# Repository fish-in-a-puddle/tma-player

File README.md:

# The Magnus Archives-themed Podcast Player

*a project by fish-in-a-puddle*

.png>) 
   .png>) 

.png>)

.png>) 

.png>)

An ESP32-based MP3 player designed to look like a handheld tape recorder like the one used in the podcast "The Magnus Archives" containing every episode of the podcast. It uses a DFPlayer Mini module to play the audio and 11 SK6812E LEDs to add green lighting under the control buttons and "speaker" grill. A 0.91" OLED display allows you to select which episode you would like to listen to and shows what's playing.

**No AI was used in making of this project**

## Why I made this project

I started listening to The Magnus Archives, a horror podcast that tells the story through a series of tape recordings, a few months ago. Throughout the series, the tape recorders almost became characters of their own and I couldn't shake the idea of listening to the story on a replica of one. The hardest part of the project was definitely 3D-modeling the case itself, but I learned a lot about using Fusion, as well as designing PCBs.

## How to assemble 

Assembling the hardware itself should not be difficult. Once you have all the parts (as listed in Bill of Materials below) you will simply have to solder them onto their respective PCBs. To connect the two PCBs, you will need to take nine female-to-female jumper wires and connect each pin on the main PCB to its mate (5v to 5v, GND to GND, DIN to DIN, etc.). To connect the OLED screen to the main PCB, take four more female-to-female jumper wires and connect the pins of the display to the pin headers on the PCB as shown:

.png>)

You will also need to wire the battery, charging board, step-up module and on/off switch as shown. These parts will be arranged in the case later, so it's important not to make the wires too short or too long.

.png>)

Before putting the whole thing together, you will need to flash the firmware to the ESP32, as it will not be accessible when the main PCB is in the case. To flash the code, you will need to have the Arduino IDE installed (download the latest version [here](https://www.arduino.cc/en/software/)). You will also need to have the "esp32" board pack and a few useful libraries installed, which is very easy to do. Just go to "Boards" and search "esp32" and click install on the pack. Make sure that you select the pack with the title in all lowercase. To download the libraries, go the "Libraries" and install these libraries:

- Adafruit_GFX
- Adafruit_SSD1306
- FastLed
- DFPlayerMini_Fast

 Once your IDE is all set up, go to the file "[player-code.ino](https://github.com/fish-in-a-puddle/tma-player/blob/main/player-code.ino)" and copy its contents. Paste them into the IDE. Connect the ESP32 to your computer via USB. Select your board and port in the dropdown menu at the top of your screen and click "Upload". Boom! Code uploaded!

 The code is not the only thing you'll need to download, though. The DFPlayer Mini is a tiny MP3 player that reads audio files from a microSD card. The files have to be named and organized a certain way, though, in order for the DFPlayer to be able to play them. But we're getting a bit ahead of ourselves. Before organizing the files, you need to download them. Unfortunately, I can't provide them all here as the podcast is not mine to distribute, but I can show you how to get them yourself. You can download them all from YouTube with a third-party downloader like [this one](https://apps.microsoft.com/detail/xpffdcd2ps6dgh?hl=en-US&gl=CA) that I used. All 200 episodes can be found on [this playlist](https://www.youtube.com/playlist?list=PLSbuB1AyaJk8zTF3nE2KRxuixG_A5gBKJ) and you can download the entire playlist at once (plus the Oh... Hello. extra [here](https://youtu.be/0ue0QZ2ED9w?si=zBTRZmKF8gP67J3-)). Be forewarned, it may take several hours and altogether is about 4.5GB. When the files are downloaded, copy them over to your microSD card (which must be formatted as FAT32!) and rename them as 0001, 0002, 0003, etc. If you need more info, check out [this article](https://printed-droid.com/kb/dfplayer-mini-guide/) by Printed Droid - it helped me a lot. If you want, you can also cut out some of the ads in an audio editing software like Audacity.

Back to the hardware! 3D print the top and bottom of the case and and place the main PCB inside the bottom part. The microSD card slot and headphone jack should line up with the holes on the top of the case. Next, take the side PCB and fit it into the large slot on the right side of the bottom part. Secure it in place with electrical tape so it doesn't slide. Right next to the headphone jack, there is a large slot for the charging board. Position the board so the charging port is accessible and secure it with electrical tape. Do the same for the on/off switch slot above it. Place the OLED display on the top part so it is visible through the rectangular hole and - you guessed  it - secure it with electrical tape. As you put the top and bottom parts together, you may have to get a little creative arranging the battery and wires in the case. Once everything is packed away, screw together the top and bottom with four M3 screws.

## Bill of Materials

|Part                       |Quantity|My Source                                                                                                                                                                                                                                                                                                                                                                                                                                                                                                                                                                                                                                                                                                                                                                     |Price (USD)|Shipping      |Alternate Source (if necessary)                                                                                                                                                                                                                                                                                                                                                                                                                                                                                                                                                                                                                                                                                                                                                        |Price (USD)|Shipping      |Notes                                             |
|---------------------------|--------|------------------------------------------------------------------------------------------------------------------------------------------------------------------------------------------------------------------------------------------------------------------------------------------------------------------------------------------------------------------------------------------------------------------------------------------------------------------------------------------------------------------------------------------------------------------------------------------------------------------------------------------------------------------------------------------------------------------------------------------------------------------------------|-----------|--------------|---------------------------------------------------------------------------------------------------------------------------------------------------------------------------------------------------------------------------------------------------------------------------------------------------------------------------------------------------------------------------------------------------------------------------------------------------------------------------------------------------------------------------------------------------------------------------------------------------------------------------------------------------------------------------------------------------------------------------------------------------------------------------------------|-----------|--------------|--------------------------------------------------|
|Seeeduino Xiao ESP-32-C3   | 1      | https://www.aliexpress.com/item/1005008791937363.html?spm=a2g0o.productlist.main.1.4de91acfmMRQxW&algo_pvid=2fee8b63-2bf0-4724-bf66-3179fd38bab1&algo_exp_id=2fee8b63-2bf0-4724-bf66-3179fd38bab1-0&pdp_ext_f=%7B%22order%22%3A%221596%22%2C%22eval%22%3A%221%22%2C%22fromPage%22%3A%22search%22%7D&pdp_npi=6%40dis%21CAD%2113.05%2110.17%21%21%219.07%217.07%21%402101e75417932184264203459e0fe8%2112000052930246748%21sea%21CA%210%21ABX%211%210%21n_tag%3A-29910%3Bd%3Aae79d1aa%3Bm03_new_user%3A-29895%3BpisId%3A5000000218656158&curPageLogUid=wpoppYNjFX4K&utparam-url=scene%3Asearch%7Cquery_from%3A%7Cx_object_id%3A1005008791937363%7C_p_origin_prod%3A                                                                                                             | $9.27     | Free shipping| x                                                                                                                                                                                                                                                                                                                                                                                                                                                                                                                                                                                                                                                                                                                                                                                     | x         | x            | None                                             |
|DFPlayer Mini (YX5200-24QS)| 1      | https://www.aliexpress.com/item/1005003432670517.html?spm=a2g0o.productlist.main.6.b79435a6qtJZhj&algo_pvid=8a43199a-29af-4fc8-b324-c76739e5a8f2&algo_exp_id=8a43199a-29af-4fc8-b324-c76739e5a8f2-5&pdp_ext_f=%7B%22order%22%3A%221037%22%2C%22eval%22%3A%221%22%2C%22fromPage%22%3A%22search%22%7D&pdp_npi=6%40dis%21CAD%215.17%214.19%21%21%2123.96%2119.42%21%402101c28d17932189515971049e0efb%2112000025764114712%21sea%21CA%210%21ABX%211%210%21n_tag%3A-29910%3Bd%3Aae79d1aa%3Bm03_new_user%3A-29895&curPageLogUid=lcZ3ZxaTiNQR&utparam-url=scene%3Asearch%7Cquery_from%3A%7Cx_object_id%3A1005003432670517%7C_p_origin_prod%3A                                                                                                                                        | $3.65     | $5.42        | x                                                                                                                                                                                                                                                                                                                                                                                                                                                                                                                                                                                                                                                                                                                                                                                     | x         | x            | None                                             |
|Headphone jack             | 1      | https://www.aliexpress.com/item/4000114275750.html?spm=a2g0o.productlist.main.14.45ce323943IJGD&algo_pvid=0fef7f45-504e-4663-8247-9c40bcd4e426&algo_exp_id=0fef7f45-504e-4663-8247-9c40bcd4e426-13&pdp_ext_f=%7B%22order%22%3A%2236%22%2C%22eval%22%3A%221%22%2C%22fromPage%22%3A%22search%22%7D&pdp_npi=6%40dis%21CAD%212.93%211.71%21%21%2113.58%217.93%21%402101ca8b17932239827126302e0f03%2112000032841975173%21sea%21CA%210%21ABX%211%210%21n_tag%3A-29910%3Bd%3Aae79d1aa%3Bm03_new_user%3A-29895%3BpisId%3A5000000218656158&curPageLogUid=AsbevJNFO0kb&utparam-url=scene%3Asearch%7Cquery_from%3A%7Cx_object_id%3A4000114275750%7C_p_origin_prod%3A                                                                                                                    | $2.18     | Free shipping| x                                                                                                                                                                                                                                                                                                                                                                                                                                                                                                                                                                                                                                                                                                                                                                                     | x         | x            | This source comes in a pack of 10                |
|0.91 OLED                  | 1      | https://www.aliexpress.com/item/1005008918700196.html?spm=a2g0o.productlist.main.2.7de8411fMeiJOd&algo_pvid=0fc6a299-644e-44f4-b982-0728ee1bc7f9&algo_exp_id=0fc6a299-644e-44f4-b982-0728ee1bc7f9-1&pdp_ext_f=%7B%22order%22%3A%22908%22%2C%22spu_best_type%22%3A%22price%22%2C%22eval%22%3A%221%22%2C%22fromPage%22%3A%22search%22%7D&pdp_npi=6%40dis%21CAD%213.60%211.74%21%21%212.47%211.19%21%40210327b017946691312165659e0e37%2112000047202792616%21sea%21CA%210%21ABX%211%210%21n_tag%3A-29910%3Bd%3Aefcbf61%3Bm03_new_user%3A-29895%3BpisId%3A5000000218625931&curPageLogUid=dVpT9IM6Sb9L&utparam-url=scene%3Asearch%7Cquery_from%3A%7Cx_object_id%3A1005008918700196%7C_p_origin_prod%3A                                                                             | $2.58     | Free shipping| x                                                                                                                                                                                                                                                                                                                                                                                                                                                                                                                                                                                                                                                                                                                                                                                     | x         | x            | Buy the version with white text                  |
|Toggle switch              | 1      | https://www.aliexpress.com/item/1005008304338583.html?spm=a2g0o.productlist.main.4.7a6915bapGlbZB&aem_p4p_detail=202611211749531201418159040720001920699&algo_pvid=33cdea45-54ac-4164-86e0-36b4e3f8295f&algo_exp_id=33cdea45-54ac-4164-86e0-36b4e3f8295f-3&pdp_ext_f=%7B%22order%22%3A%223730%22%2C%22eval%22%3A%221%22%2C%22fromPage%22%3A%22search%22%7D&pdp_npi=6%40dis%21CAD%216.66%211.75%21%21%2130.28%217.92%21%402101c4ea17953121930127537e0ff8%2112000044555585173%21sea%21CA%210%21ABX%211%210%21n_tag%3A-29910%3Bd%3Aefcbf61%3Bm03_new_user%3A-29895%3BpisId%3A5000000218625935&curPageLogUid=Mz6zwQEAy92a&utparam-url=scene%3Asearch%7Cquery_from%3A%7Cx_object_id%3A1005008304338583%7C_p_origin_prod%3A&search_p4p_id=202611211749531201418159040720001920699_1| $4.64     | Free shipping| x                                                                                                                                                                                                                                                                                                                                                                                                                                                                                                                                                                                                                                                                                                                                                                                     | x         | x            |Comes in pack of 10                               |
|Charging board             | 1      | https://www.aliexpress.com/item/1005007176376691.html?spm=a2g0o.productlist.main.5.78ae2a94npf7VK&algo_pvid=84e47fdb-b963-4705-8d50-a8167387f458&algo_exp_id=84e47fdb-b963-4705-8d50-a8167387f458-4&pdp_ext_f=%7B%22order%22%3A%224529%22%2C%22eval%22%3A%221%22%2C%22fromPage%22%3A%22search%22%7D&pdp_npi=6%40dis%21CAD%213.56%211.73%21%21%2116.39%217.96%21%4021030f8317921823444828610e0f04%2112000044697950819%21sea%21CA%210%21ABX%211%210%21n_tag%3A-29910%3Bd%3A59ac8ea0%3Bm03_new_user%3A-29895%3BpisId%3A5000000218640858&curPageLogUid=oX28Jdw7Dcfm&utparam-url=scene%3Asearch%7Cquery_from%3A%7Cx_object_id%3A1005007176376691%7C_p_origin_prod%3A                                                                                                              | $2.50     | Free shipping| x                                                                                                                                                                                                                                                                                                                                                                                                                                                                                                                                                                                                                                                                                                                                                                                     | x         | x            | Buy Type-c version                               |
|3.7 to 5v converter        | 1      | https://www.aliexpress.com/item/1005009886614988.html?spm=a2g0o.productlist.main.15.7bd941bahfQ4ew&algo_pvid=f71aa114-ff81-4c28-bada-3685d00938ec&algo_exp_id=f71aa114-ff81-4c28-bada-3685d00938ec-12&pdp_ext_f=%7B%22order%22%3A%22319%22%2C%22eval%22%3A%221%22%2C%22fromPage%22%3A%22search%22%7D&pdp_npi=6%40dis%21CAD%211.83%211.19%21%21%211.26%210.82%21%402101d3fe17921826331035682e0fbb%2112000050482123027%21sea%21CA%210%21ABX%211%210%21n_tag%3A-29910%3Bd%3A59ac8ea0%3Bm03_new_user%3A-29895&curPageLogUid=CW98wpodDnyn&utparam-url=scene%3Asearch%7Cquery_from%3A%7Cx_object_id%3A1005009886614988%7C_p_origin_prod%3A                                                                                                                                         | $1.28     | $6.00        | x                                                                                                                                                                                                                                                                                                                                                                                                                                                                                                                                                                                                                                                                                                                                                                                     | x         | x            | None                                             |
|Lipo battery               | 1      | https://www.aliexpress.com/item/1005009939339870.html?spm=a2g0o.productlist.main.18.73b46ee1murCfL&algo_pvid=50d0af34-6228-4874-9fac-6284729655b3&algo_exp_id=50d0af34-6228-4874-9fac-6284729655b3-17&pdp_ext_f=%7B%22order%22%3A%22206%22%2C%22spu_best_type%22%3A%22price%22%2C%22eval%22%3A%221%22%2C%22fromPage%22%3A%22search%22%7D&pdp_npi=6%40dis%21CAD%2110.75%216.45%21%21%2149.81%2129.89%21%4021030cd817932242519431859e0d3f%2112000050631004477%21sea%21CA%210%21ABX%211%210%21n_tag%3A-29910%3Bd%3Aae79d1aa%3Bm03_new_user%3A-29895&curPageLogUid=QlHpURKrjpsB&utparam-url=scene%3Asearch%7Cquery_from%3A%7Cx_object_id%3A1005009939339870%7C_p_origin_prod%3A                                                                                                  | $7.53     | $2.96        | x                                                                                                                                                                                                                                                                                                                                                                                                                                                                                                                                                                                                                                                                                                                                                                                     | x         | x            | None                                             |
|SK6812MINI-E LED           | 11     | Leftovers from Hack Club's Hackpad Kit (https://hackpad.hackclub.com/)                                                                                                                                                                                                                                                                                                                                                                                                                                                                                                                                                                                                                                                                                                       | $0        | $0           | https://www.aliexpress.com/item/1005007863635868.html?spm=a2g0o.productlist.main.1.71e51c3cifbRkD&algo_pvid=96cd1d50-48f6-47d0-9c8d-db0703947e2a&algo_exp_id=96cd1d50-48f6-47d0-9c8d-db0703947e2a-0&pdp_ext_f=%7B%22order%22%3A%22635%22%2C%22eval%22%3A%221%22%2C%22fromPage%22%3A%22search%22%7D&pdp_npi=6%40dis%21CAD%216.87%211.75%21%21%214.68%211.19%21%402101de2517953112525471063e0eec%2112000042594617264%21sea%21CA%210%21ABX%211%210%21n_tag%3A-29910%3Bd%3Aefcbf61%3Bm03_new_user%3A-29895%3BpisId%3A5000000218625935&curPageLogUid=0hEvfxi8ywtW&utparam-url=scene%3Asearch%7Cquery_from%3A%7Cx_object_id%3A1005007863635868%7C_p_origin_prod%3A                                                                                                                          | $4.78     | Free shipping| Alternate source comes in pack of 100            |
|1N4148 Diode               | 1      | Leftovers from Hack Club's Hackpad Kit (https://hackpad.hackclub.com)                                                                                                                                                                                                                                                                                                                                                                                                                                                                                                                                                                                                                                                                                                        | $0        | $0           | https://www.aliexpress.com/item/1005012285965228.html?spm=a2g0o.productlist.main.28.79e7482d6HQ6Nf&aem_p4p_detail=202611211738254444529954834100000471533&algo_pvid=434f4d44-b9f7-4691-8bfc-d5242381183e&algo_exp_id=434f4d44-b9f7-4691-8bfc-d5242381183e-27&pdp_ext_f=%7B%22order%22%3A%2211%22%2C%22spu_best_type%22%3A%22price%22%2C%22eval%22%3A%221%22%2C%22fromPage%22%3A%22search%22%7D&pdp_npi=6%40dis%21CAD%212.22%211.82%21%21%2110.09%218.27%21%402101c4b817953115053577203e0e78%2112000057989572495%21sea%21CA%210%21ABX%211%210%21n_tag%3A-29910%3Bd%3Aefcbf61%3Bm03_new_user%3A-29895&curPageLogUid=KVPwmbDF8rbQ&utparam-url=scene%3Asearch%7Cquery_from%3A%7Cx_object_id%3A1005012285965228%7C_p_origin_prod%3A&search_p4p_id=202611211738254444529954834100000471533_7| $6.39     | Free shipping| Alternate source comes in pack of 100            |
|Cherry MX keyswitches      | 5      | Leftovers from Hack Club's Hackpad Kit (https://hackpad.hackclub.com)                                                                                                                                                                                                                                                                                                                                                                                                                                                                                                                                                                                                                                                                                                        | $0        | $0           | https://www.aliexpress.com/item/1005012832907656.html?spm=a2g0o.productlist.main.6.516b44cc2K1o9K&algo_pvid=d45f9856-152a-4c3e-987f-c93a21a25b67&algo_exp_id=d45f9856-152a-4c3e-987f-c93a21a25b67-5&pdp_ext_f=%7B%22order%22%3A%2260%22%2C%22eval%22%3A%221%22%2C%22fromPage%22%3A%22search%22%7D&pdp_npi=6%40dis%21CAD%218.13%211.75%21%21%215.54%211.19%21%402101e56817953146701488274e0e89%2112000059458181010%21sea%21CA%210%21ABX%211%210%21n_tag%3A-29910%3Bd%3Aefcbf61%3Bm03_new_user%3A-29895%3BpisId%3A5000000218625935&curPageLogUid=AAqFQ5bkuN9i&utparam-url=scene%3Asearch%7Cquery_from%3A%7Cx_object_id%3A1005012832907656%7C_p_origin_prod%3A                                                                                                                           | $5.66     | Free shipping| Alternate source comes in pack of 10             |
|Keycaps                    | 5      | Leftovers from Hack Club's Hackpad Kit (https://hackpad.hackclub.com)                                                                                                                                                                                                                                                                                                                                                                                                                                                                                                                                                                                                                                                                                                        | $0        | $0           | https://www.aliexpress.com/item/1005010545409350.html?spm=a2g0o.productlist.main.21.7734599cbfPriz&algo_pvid=cc549d13-fe82-422f-8342-e8792835ce0d&algo_exp_id=cc549d13-fe82-422f-8342-e8792835ce0d-20&pdp_ext_f=%7B%22order%22%3A%22388%22%2C%22eval%22%3A%221%22%2C%22fromPage%22%3A%22search%22%7D&pdp_npi=6%40dis%21CAD%215.33%211.75%21%21%213.63%211.19%21%402101c4b817953149577943262e0efc%2112000052767672810%21sea%21CA%210%21ABX%211%210%21n_tag%3A-29910%3Bd%3Aefcbf61%3Bm03_new_user%3A-29895%3BpisId%3A5000000218625935&curPageLogUid=jElAVqFtryO5&utparam-url=scene%3Asearch%7Cquery_from%3A%7Cx_object_id%3A1005010545409350%7C_p_origin_prod%3A                                                                                                                        | $3.71     | Free shipping| Alternate source comes in pack of 10             |
|25mm M3 screws             | 4      | https://www.aliexpress.com/item/1005005070119421.html?spm=a2g0o.productlist.main.1.2b886e1fgwFFsl&algo_pvid=aae8f3ad-208c-46b6-ab58-f4c01dd6ced7&algo_exp_id=aae8f3ad-208c-46b6-ab58-f4c01dd6ced7-0&pdp_ext_f=%7B%22order%22%3A%2239084%22%2C%22spu_best_type%22%3A%22price%22%2C%22eval%22%3A%221%22%2C%22fromPage%22%3A%22search%22%7D&pdp_npi=6%40dis%21CAD%212.51%211.75%21%21%211.71%211.19%21%4021030f8317955492549322586e0eb6%2112000031519353305%21sea%21CA%210%21ABX%211%210%21n_tag%3A-29910%3Bd%3Aefcbf61%3Bm03_new_user%3A-29895%3BpisId%3A5000000218625934&curPageLogUid=QeZJmcAGx4kg&utparam-url=scene%3Asearch%7Cquery_from%3A%7Cx_object_id%3A1005005070119421%7C_p_origin_prod%3A                                                                           | $3.86     | Free shipping| x                                                                                                                                                                                                                                                                                                                                                                                                                                                                                                                                                                                                                                                                                                                                                                                     | x         | x            | Comes in pack of 50                              |
|1kohm resistor             | 4      | https://www.aliexpress.com/item/1005002580178929.html?spm=a2g0o.productlist.main.22.166b6d60KBE4U0&aem_p4p_detail=202611211806376467483684059500001906962&algo_pvid=edbc9152-e65f-4729-bbd9-f900f122d453&algo_exp_id=edbc9152-e65f-4729-bbd9-f900f122d453-19&pdp_ext_f=%7B%22order%22%3A%22679%22%2C%22eval%22%3A%221%22%2C%22fromPage%22%3A%22search%22%7D&pdp_npi=6%40dis%21CAD%214.59%211.75%21%21%213.13%211.20%21%402101ea8f17953131974298811e08a8%2112000021245046656%21sea%21CA%210%21ABX%211%210%21n_tag%3A-29910%3Bd%3Aefcbf61%3Bm03_new_user%3A-29895%3BpisId%3A5000000218625935&curPageLogUid=Fq1QoduLe98H&utparam-url=scene%3Asearch%7Cquery_from%3A%7Cx_object_id%3A1005002580178929%7C_p_origin_prod%3A&search_p4p_id=202611211806376467483684059500001906962_5| $4.14     | Free shipping| x                                                                                                                                                                                                                                                                                                                                                                                                                                                                                                                                                                                                                                                                                                                                                                                     | x         | x            | This source comes in pack of 20                  |
|32gb MicroSD card          | 1      | https://www.aliexpress.com/item/1005007498167692.html?spm=a2g0o.productlist.main.17.fcba288bFLAcSD&algo_pvid=f6bce296-19da-42ea-9d59-f8da1a0c549c&algo_exp_id=f6bce296-19da-42ea-9d59-f8da1a0c549c-16&pdp_ext_f=%7B%22order%22%3A%2235229%22%2C%22spu_best_type%22%3A%22price%22%2C%22eval%22%3A%221%22%2C%22fromPage%22%3A%22search%22%7D&pdp_npi=6%40dis%21CAD%2112.13%211.75%21%21%218.27%211.20%21%402101ca9517953119118377072e0d41%2112000041032084439%21sea%21CA%210%21ABX%211%210%21n_tag%3A-29910%3Bd%3Aefcbf61%3Bm03_new_user%3A-29895%3BpisId%3A5000000218625936&curPageLogUid=mZfRL4Fc1bcW&utparam-url=scene%3Asearch%7Cquery_from%3A%7Cx_object_id%3A1005007498167692%7C_p_origin_prod%3A                                                                        | $8.45     | Free shipping| x                                                                                                                                                                                                                                                                                                                                                                                                                                                                                                                                                                                                                                                                                                                                                                                     | x         | x            | None                                             |
|Front PCB                  | 1      | JLCPCB                                                                                                                                                                                                                                                                                                                                                                                                                                                                                                                                                                                                                                                                                                                                                                       | $10.30    | $8.92        | x                                                                                                                                                                                                                                                                                                                                                                                                                                                                                                                                                                                                                                                                                                                                                                                     | x         | x            | Order on the JLC Desktop version for better price|
|Side PCB                   | 1      | JLCPCB                                                                                                                                                                                                                                                                                                                                                                                                                                                                                                                                                                                                                                                                                                                                                                       | $2.10     | $1.50        | x                                                                                                                                                                                                                                                                                                                                                                                                                                                                                                                                                                                                                                                                                                                                                                                     | x         | x            | Order in the JLC Desktop version for better price|
|Parts total:               | $58.62 |                                                                                                                                                                                                                                                                                                                                                                                                                                                                                                                                                                                                                                                                                                                                                                              |           |              |                                                                                                                                                                                                                                                                                                                                                                                                                                                                                                                                                                                                                                                                                                                                                                                       |           |              |                                                  |
|Shipping total:            | $24.80 |                                                                                                                                                                                                                                                                                                                                                                                                                                                                                                                                                                                                                                                                                                                                                                              |           |              |                                                                                                                                                                                                                                                                                                                                                                                                                                                                                                                                                                                                                                                                                                                                                                                       |           |              |                                                  |
|Final total:               | $83.42 |                                                                                                                                                                                                                                                                                                                                                                                                                                                                                                                                                                                                                                                                                                                                                                              |           |              |                                                                                                                                                                                                                                                                                                                                                                                                                                                                                                                                                                                                                                                                                                                                                                                       |           |              |                                                  |

## Credits

References, libraries and Kicad footprints I used to make this project

- Seeeduino Xiao ESP-32-C3 Kicad footprint - https://gitlab.fabcloud.org/ricardo.marques/kicad/-/blob/master/fab.pretty/SeeedStudio_XIAO_ESP32C3.kicad_mod
- Seeeduino Xiao ESP-32-C3 Kicad symbol - https://github.com/VectorSpaceHQ/XIAO_ESP32C3/blob/main/xiao_esp32c3.kicad_sym 
- DFPlayer Mini Kicad footprint - https://github.com/MrChunckuee-Electronics/KiCad_Libraries/blob/master/footprints/MCE_Modules.pretty/DFPlayer_MiniMP3.kicad_mod
- DFPlayer Mini Kicad schematic symbol - https://github.com/MrChunckuee-Electronics/KiCad_Libraries/blob/master/symbols/MCE_Modules.kicad_sym
- DFPlayer Mini wiring - https://reprage.com/posts/2018-05-08-dfplayer-mini-cheat-sheet/, https://www.reddit.com/r/arduino/comments/1n1itlh/getting_nothing_out_of_dfplayer/, https://www.printed-droid.com/kb/dfplayer-mini-guide/
- FastLED library examples: https://github.com/FastLED/FastLED/blob/master/cookbook/basic-patterns/animations.md
- DFPlayerMini_Fast library example: https://github.com/PowerBroker2/DFPlayerMini_Fast/blob/master/examples/example/example.ino
- Adafruit SSD1306 OLED library: https://github.com/adafruit/Adafruit_SSD1306
- YouTube downloader/mp3 converter for Windows: https://apps.microsoft.com/detail/xpffdcd2ps6dgh?hl=en-US&gl=CA
- The Magnus Archives full series on YouTube: https://www.youtube.com/playlist?list=PLSbuB1AyaJk8zTF3nE2KRxuixG_A5gBKJ
- Cherry MX keycap used for model: https://www.printables.com/model/118708-simple-cherry-mx-keycap/files
- Kicad care package from Hackpad program (used SK6812MINI-E footprint): https://github.com/hackclub/hackpad/releases/tag/v0.1-bugfix

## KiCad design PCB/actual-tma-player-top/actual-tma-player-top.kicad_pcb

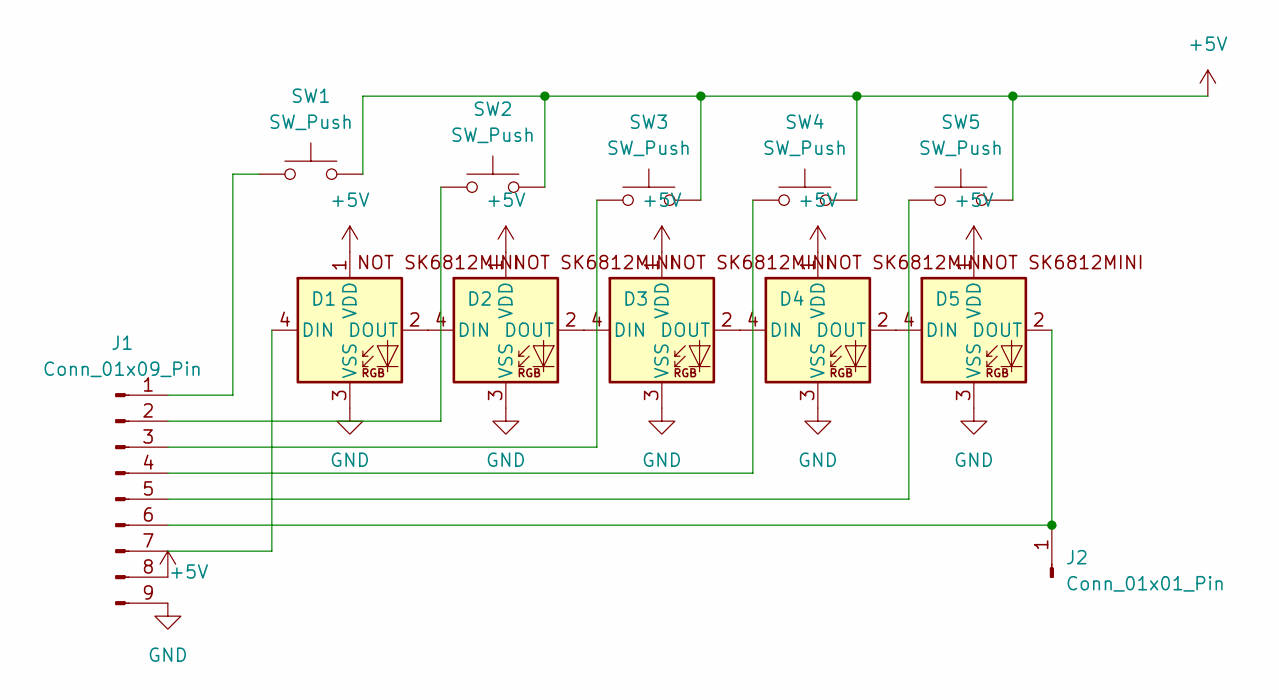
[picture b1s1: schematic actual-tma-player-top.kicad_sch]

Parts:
D1, D2, D3, D4, D5: SK6812MINI-E; SK6812MINI-E_fixed
J1: Conn_01x09_Pin; PinHeader_1x09_P1.00mm_Vertical
J2: Conn_01x01_Pin; PinHeader_1x01_P1.00mm_Vertical
SW1, SW2, SW3, SW4, SW5: SW_Push; SW_Cherry_MX_1.00u_PCB

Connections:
+5V: D1.1 (VDD), D2.1 (VDD), D3.1 (VDD), D4.1 (VDD), D5.1 (VDD), J1.8, SW1.2, SW2.2, SW3.2, SW4.2, SW5.2
GND: D1.3 (VSS), D2.3 (VSS), D3.3 (VSS), D4.3 (VSS), D5.3 (VSS), J1.9
unnamed: D1.4 (DIN), J1.7
unnamed: D1.2 (DOUT), D2.4 (DIN)
unnamed: D2.2 (DOUT), D3.4 (DIN)
unnamed: D3.2 (DOUT), D4.4 (DIN)
unnamed: D4.2 (DOUT), D5.4 (DIN)
unnamed: D5.2 (DOUT), J1.6, J2.1 (Pin_1_1)
unnamed: J1.1, SW1.1
unnamed: J1.2, SW2.1
unnamed: J1.3, SW3.1
unnamed: J1.4, SW4.1
unnamed: J1.5, SW5.1

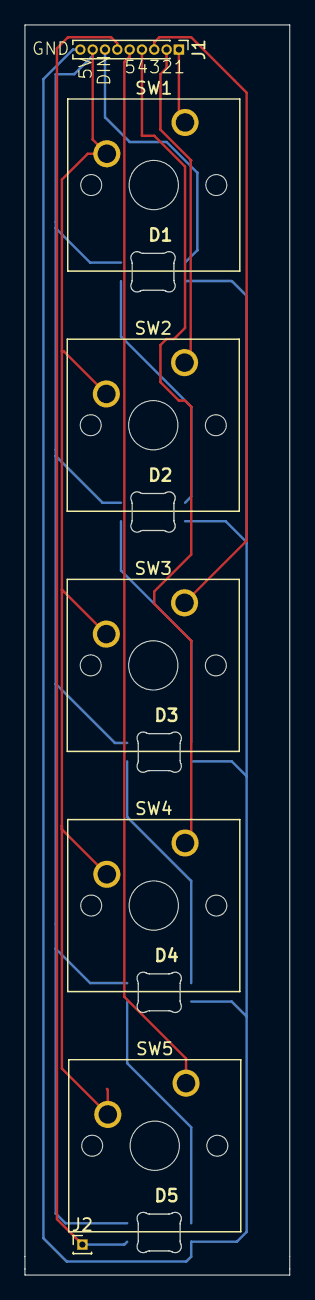
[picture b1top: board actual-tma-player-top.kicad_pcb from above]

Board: 2 copper layers, 21.5 x 101.5 mm, 12 parts (0 on the bottom side), 13 nets.

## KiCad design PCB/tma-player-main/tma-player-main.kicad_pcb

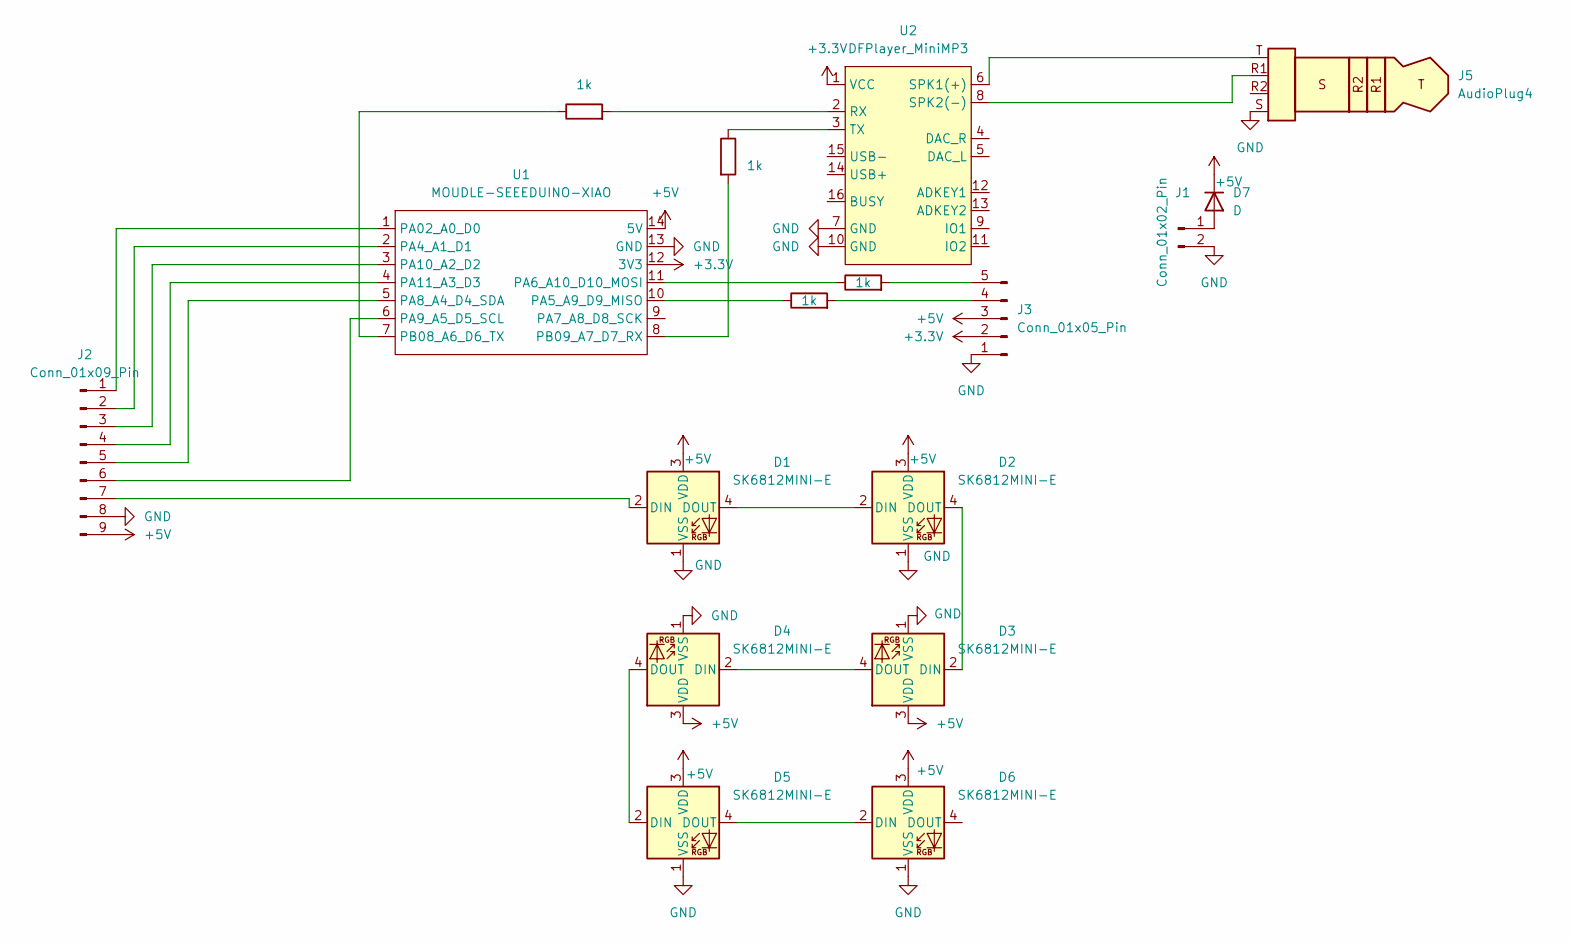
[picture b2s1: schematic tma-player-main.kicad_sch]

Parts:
D1, D2, D3, D4, D5, D6: SK6812MINI-E; LED_SK6812MINI-E_3.2x2.8mm_P1.5mm_ReverseMount
D7: D; D_DO-35_SOD27_P7.62mm_Horizontal
J1: Conn_01x02_Pin; PinHeader_1x02_P1.00mm_Horizontal
J2: Conn_01x09_Pin; PinHeader_1x09_P1.00mm_Vertical
J3: Conn_01x05_Pin; PinHeader_1x05_P1.00mm_Vertical
J5: AudioPlug4; Jack_3.5mm_PJ320D_Horizontal
R1, R2: 1k; R_Axial_DIN0309_L9.0mm_D3.2mm_P15.24mm_Horizontal
R3, R4: 1k; R_Axial_DIN0207_L6.3mm_D2.5mm_P15.24mm_Horizontal
U1: MOUDLE-SEEEDUINO-XIAO; SeeedStudio_XIAO_ESP32C3
U2: DFPlayer_MiniMP3

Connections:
+3.3V: J3.2, U1.12 (3V3), U2.1 (VCC)
+5V: D1.3 (VDD), D2.3 (VDD), D3.3 (VDD), D4.3 (VDD), D5.3 (VDD), D6.3 (VDD), D7.1 (K), J2.9, J3.3, U1.14 (5V); also elsewhere on the board
GND: D1.1 (VSS), D2.1 (VSS), D3.1 (VSS), D4.1 (VSS), D5.1 (VSS), D6.1 (VSS), J1.2, J2.8, J3.1, J5.S, U1.13 (GND), U2.7 (GND), U2.10 (GND)
unnamed: D1.2 (DIN), J2.7
unnamed: D1.4 (DOUT), D2.2 (DIN)
unnamed: D2.4 (DOUT), D3.2 (DIN)
unnamed: D3.4 (DOUT), D4.2 (DIN)
unnamed: D4.4 (DOUT), D5.2 (DIN)
unnamed: D5.4 (DOUT), D6.2 (DIN)
unnamed 9: D7.2 (A), J1.1; also elsewhere on the board
unnamed: J2.1, U1.1 (PA02_A0_D0)
unnamed: J2.2, U1.2 (PA4_A1_D1)
unnamed: J2.3, U1.3 (PA10_A2_D2)
unnamed: J2.4, U1.4 (PA11_A3_D3)
unnamed: J2.5, U1.5 (PA8_A4_D4_SDA)
unnamed: J2.6, U1.6 (PA9_A5_D5_SCL)
unnamed: J3.4, R4.2
unnamed: J3.5, R3.2
unnamed: R4.1, U1.10 (PA5_A9_D9_MISO)
unnamed: R3.1, U1.11 (PA6_A10_D10_MOSI)
unnamed: R1.1, U1.7 (PB08_A6_D6_TX)
unnamed: R2.2, U1.8 (PB09_A7_D7_RX)
unnamed: R1.2, U2.2 (RX)
unnamed: J5.T, U2.6 (SPK1(+))
unnamed: J5.R1, U2.8 (SPK2(-))
unnamed: R2.1, U2.3 (TX)

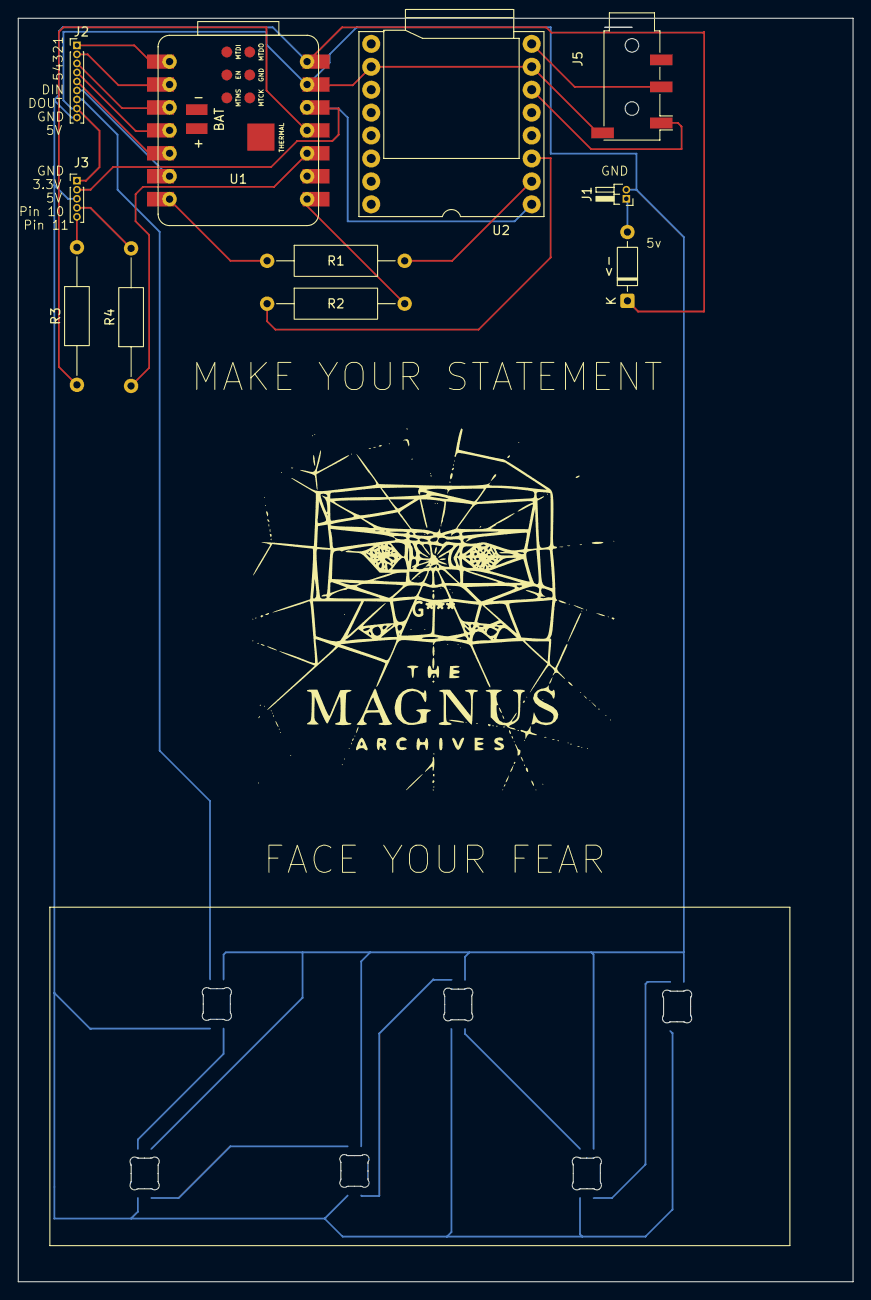
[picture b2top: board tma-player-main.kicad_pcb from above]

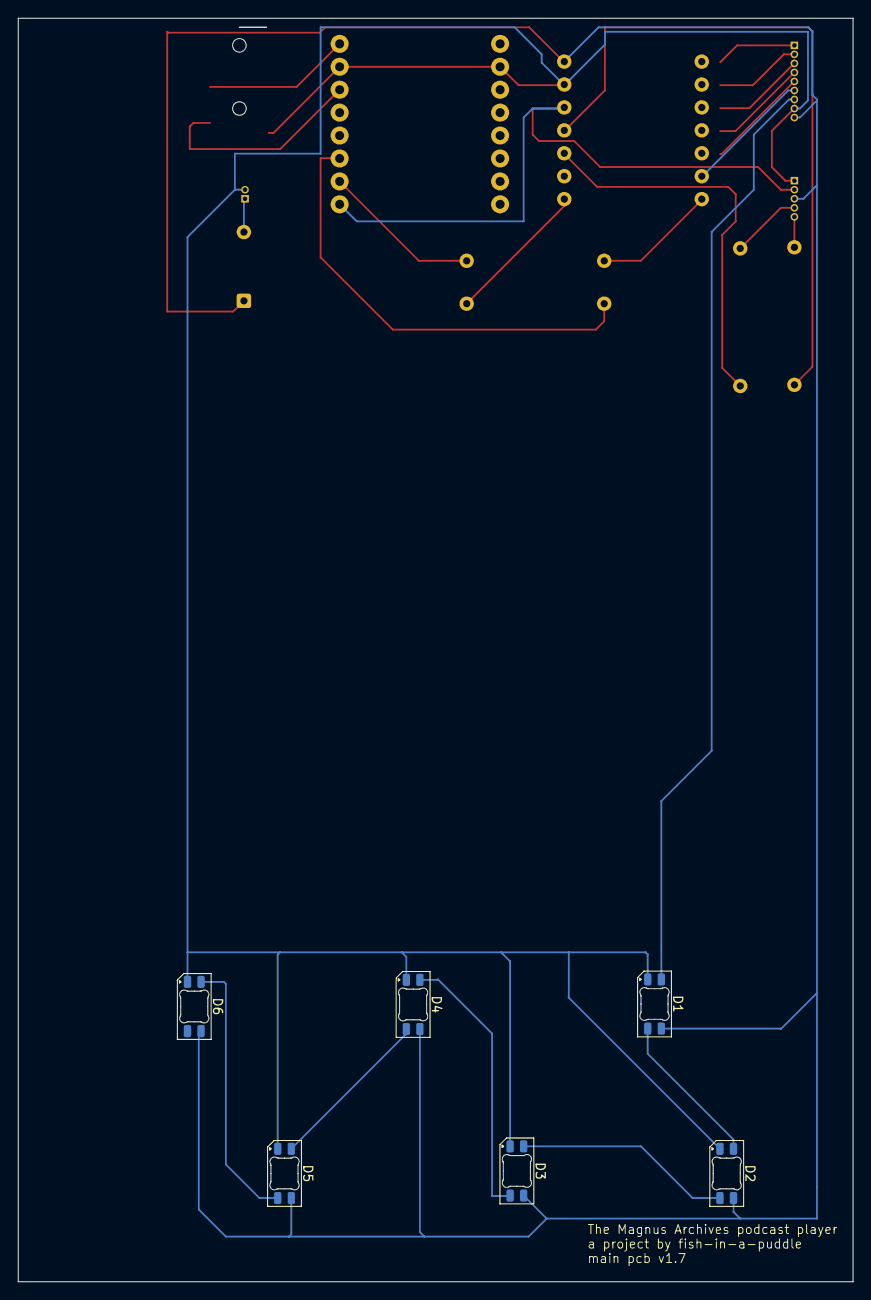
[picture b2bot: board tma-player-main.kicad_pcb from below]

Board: 2 copper layers, 92.5 x 140.0 mm, 17 parts (6 on the bottom side), 26 nets.

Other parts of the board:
<-: D; D_DO-35_SOD27_P7.62mm_Horizontal

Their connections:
+5V: <-.1 (K); also elsewhere on the board
unnamed 9: <-.2 (A); also elsewhere on the board
